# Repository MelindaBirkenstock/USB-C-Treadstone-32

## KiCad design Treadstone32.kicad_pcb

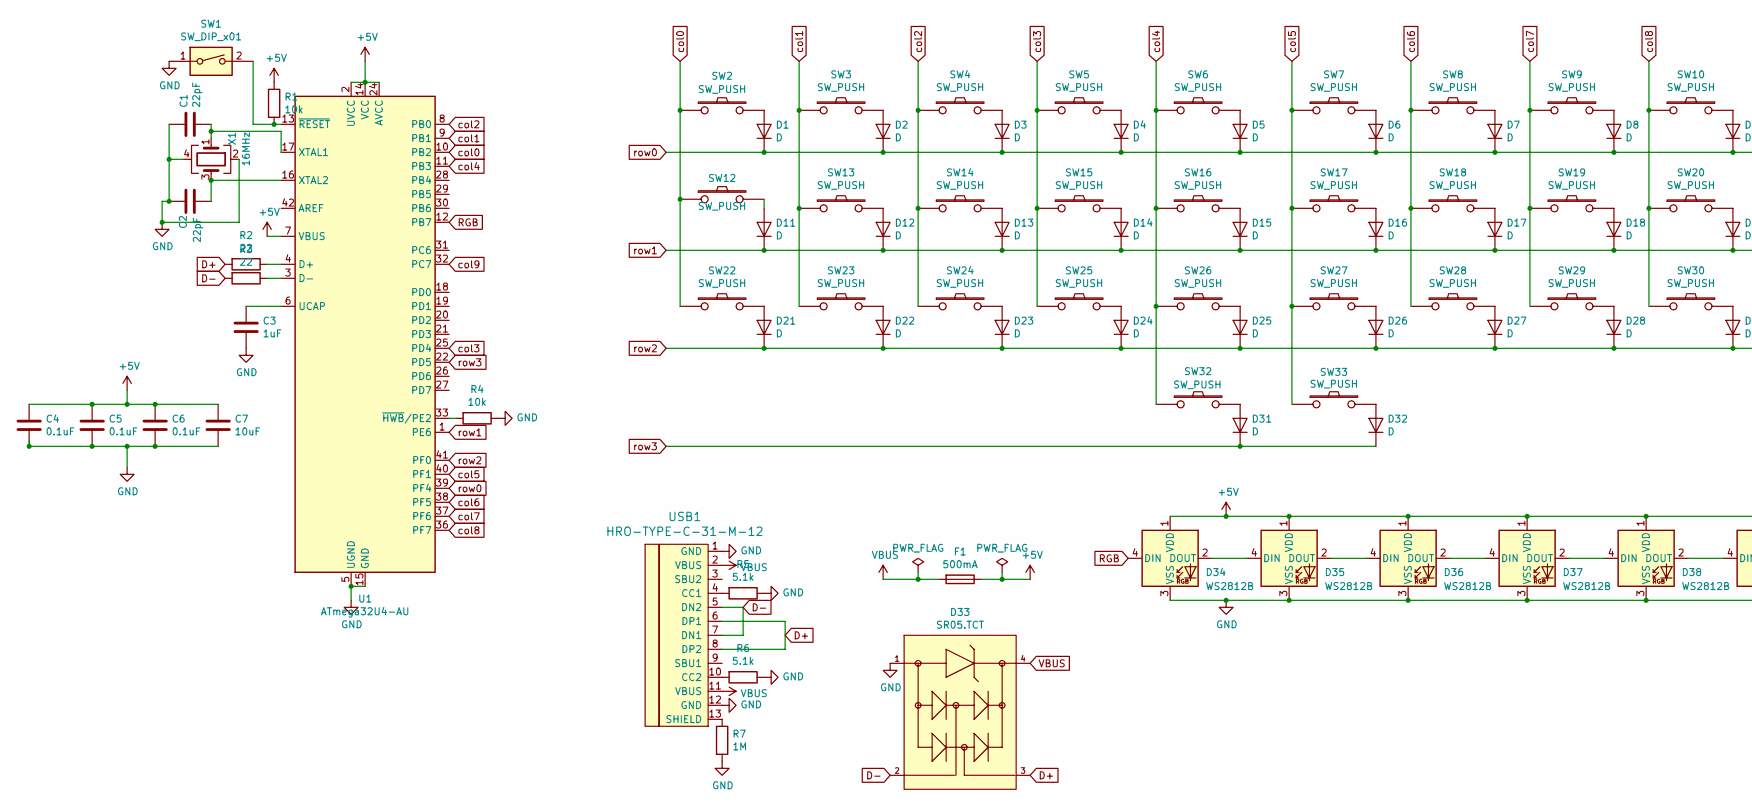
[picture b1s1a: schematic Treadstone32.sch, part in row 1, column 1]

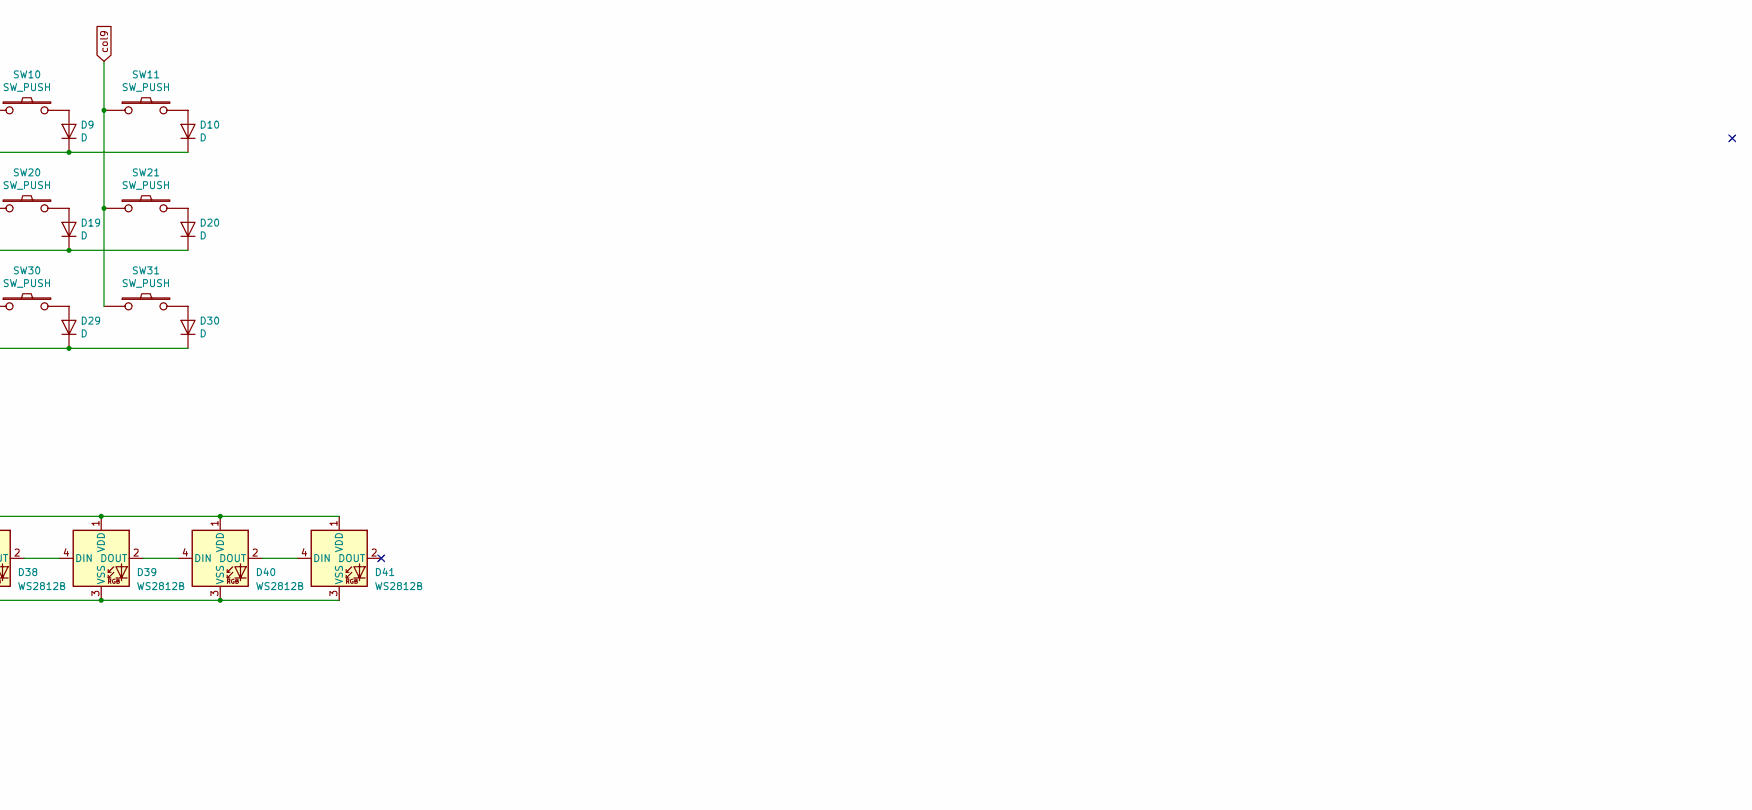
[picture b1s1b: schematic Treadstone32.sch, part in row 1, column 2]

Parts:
C1, C2: 22pF; C_0805_2012Metric
C3: 1uF; C_0805_2012Metric
C4, C5, C6: 0.1uF; C_0805_2012Metric
C7: 10uF; C_0805_2012Metric
D1, D2, D3, D4, D5, D6, D7, D8, D9, D10, D11, D12, D13, D14, D15, D16, D17, D18, D19, D20, D21, D22, D23, D24, D25, D26, D27, D28, D29, D30, D31, D32: D; D_SOD-123
D33: SR05.TCT; Semtech-SOT-143-0-0-MFG; breakdown voltage 6V; clamping voltage 20V; mouser part number 947-SR05.TCT; digikey description TVS DIODE 5V 20V SOT143-4
D34, D35, D36, D37, D38, D39, D40, D41: WS2812B; LED_WS2812B_PLCC4_5.0x5.0mm_P3.2mm
F1: 500mA; Fuse_0805_2012Metric
R1, R4: 10k; R_0805_2012Metric
R2, R3: 22; R_0805_2012Metric
R5, R6: 5.1k; R_0805_2012Metric
R7: 1M; R_0805_2012Metric
SW1: SW_DIP_x01; PinHeader_1x02_P2.00mm_Vertical
SW2, SW3, SW4, SW5, SW6, SW7, SW8, SW9, SW10, SW11, SW12, SW13, SW14, SW15, SW16, SW17, SW18, SW19, SW20, SW21, SW22, SW23, SW24, SW25, SW26, SW27, SW28, SW29, SW30, SW31, SW32, SW33: SW_PUSH; MXOnly-1U-NoLED
U1: ATmega32U4-AU; TQFP-44_10x10mm_P0.8mm
USB1: HRO-TYPE-C-31-M-12; HRO-TYPE-C-31-M-12-HandSoldering
X1: 16MHz; Crystal_SMD_3225-4Pin_3.2x2.5mm_HandSoldering

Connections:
+5V: C4.1, C5.1, C6.1, C7.1, D34.1 (VDD), D35.1 (VDD), D36.1 (VDD), D37.1 (VDD), D38.1 (VDD), D39.1 (VDD), D40.1 (VDD), D41.1 (VDD), F1.1, R1.1, U1.2 (UVCC), U1.7 (VBUS), U1.14 (VCC), U1.24 (AVCC), U1.34 (VCC), U1.44 (AVCC)
D+: D33.3 (2_I/O), R2.2, USB1.6 (DP1), USB1.8 (DP2)
D-: D33.2 (1_I/O), R3.2, USB1.5 (DN2), USB1.7 (DN1)
GND: C1.1, C2.1, C3.2, C4.2, C5.2, C6.2, C7.2, D33.1 (ANODE), D34.3 (VSS), D35.3 (VSS), D36.3 (VSS), D37.3 (VSS), D38.3 (VSS), D39.3 (VSS), D40.3 (VSS), D41.3 (VSS), R4.1, R5.1, R6.1, R7.2, SW1.1, U1.5 (UGND), U1.15 (GND), U1.23 (GND), U1.35 (GND), U1.43 (GND), USB1.1 (GND), USB1.12 (GND), X1.2, X1.4
unnamed: C1.2, U1.17 (XTAL1), X1.1
unnamed: C2.2, U1.16 (XTAL2), X1.3
unnamed: C3.1, U1.6 (UCAP)
unnamed: D1.2 (A), SW2.2
unnamed: D2.2 (A), SW3.2
unnamed: D3.2 (A), SW4.2
unnamed: D4.2 (A), SW5.2
unnamed: D5.2 (A), SW6.2
unnamed: D6.2 (A), SW7.2
unnamed: D7.2 (A), SW8.2
unnamed: D8.2 (A), SW9.2
unnamed: D9.2 (A), SW10.2
unnamed: D10.2 (A), SW11.2
unnamed: D11.2 (A), SW12.2
unnamed: D12.2 (A), SW13.2
unnamed: D13.2 (A), SW14.2
unnamed: D14.2 (A), SW15.2
unnamed: D15.2 (A), SW16.2
unnamed: D16.2 (A), SW17.2
unnamed: D17.2 (A), SW18.2
unnamed: D18.2 (A), SW19.2
unnamed: D19.2 (A), SW20.2
unnamed: D20.2 (A), SW21.2
unnamed: D21.2 (A), SW22.2
unnamed: D22.2 (A), SW23.2
unnamed: D23.2 (A), SW24.2
unnamed: D24.2 (A), SW25.2
unnamed: D25.2 (A), SW26.2
unnamed: D26.2 (A), SW27.2
unnamed: D27.2 (A), SW28.2
unnamed: D28.2 (A), SW29.2
unnamed: D29.2 (A), SW30.2
unnamed: D30.2 (A), SW31.2
unnamed: D31.2 (A), SW32.2
unnamed: D32.2 (A), SW33.2
unnamed: D34.2 (DOUT), D35.4 (DIN)
unnamed: D35.2 (DOUT), D36.4 (DIN)
unnamed: D36.2 (DOUT), D37.4 (DIN)
unnamed: D37.2 (DOUT), D38.4 (DIN)
unnamed: D38.2 (DOUT), D39.4 (DIN)
unnamed: D39.2 (DOUT), D40.4 (DIN)
unnamed: D40.2 (DOUT), D41.4 (DIN)
unnamed: R1.2, SW1.2, U1.13 (~RESET)
unnamed: R2.1, U1.4 (D+)
unnamed: R3.1, U1.3 (D-)
unnamed: R4.2, U1.33 (~HWB~/PE2)
unnamed: R5.2, USB1.4 (CC1)
unnamed: R6.2, USB1.10 (CC2)
unnamed: R7.1, USB1.13 (SHIELD)
RGB: D34.4 (DIN), U1.12 (PB7)
VBUS: D33.4 (CATHODE), F1.2, USB1.2 (VBUS), USB1.11 (VBUS)
col0: SW2.1, SW12.1, SW22.1, U1.10 (PB2)
col1: SW3.1, SW13.1, SW23.1, U1.9 (PB1)
col2: SW4.1, SW14.1, SW24.1, U1.8 (PB0)
col3: SW5.1, SW15.1, SW25.1, U1.25 (PD4)
col4: SW6.1, SW16.1, SW26.1, SW32.1, U1.11 (PB3)
col5: SW7.1, SW17.1, SW27.1, SW33.1, U1.40 (PF1)
col6: SW8.1, SW18.1, SW28.1, U1.38 (PF5)
col7: SW9.1, SW19.1, SW29.1, U1.37 (PF6)
col8: SW10.1, SW20.1, SW30.1, U1.36 (PF7)
col9: SW11.1, SW21.1, SW31.1, U1.32 (PC7)
row0: D1.1 (K), D2.1 (K), D3.1 (K), D4.1 (K), D5.1 (K), D6.1 (K), D7.1 (K), D8.1 (K), D9.1 (K), D10.1 (K), U1.39 (PF4)
row1: D11.1 (K), D12.1 (K), D13.1 (K), D14.1 (K), D15.1 (K), D16.1 (K), D17.1 (K), D18.1 (K), D19.1 (K), D20.1 (K), U1.1 (PE6)
row2: D21.1 (K), D22.1 (K), D23.1 (K), D24.1 (K), D25.1 (K), D26.1 (K), D27.1 (K), D28.1 (K), D29.1 (K), D30.1 (K), U1.41 (PF0)
row3: D31.1 (K), D32.1 (K), U1.22 (PD5)

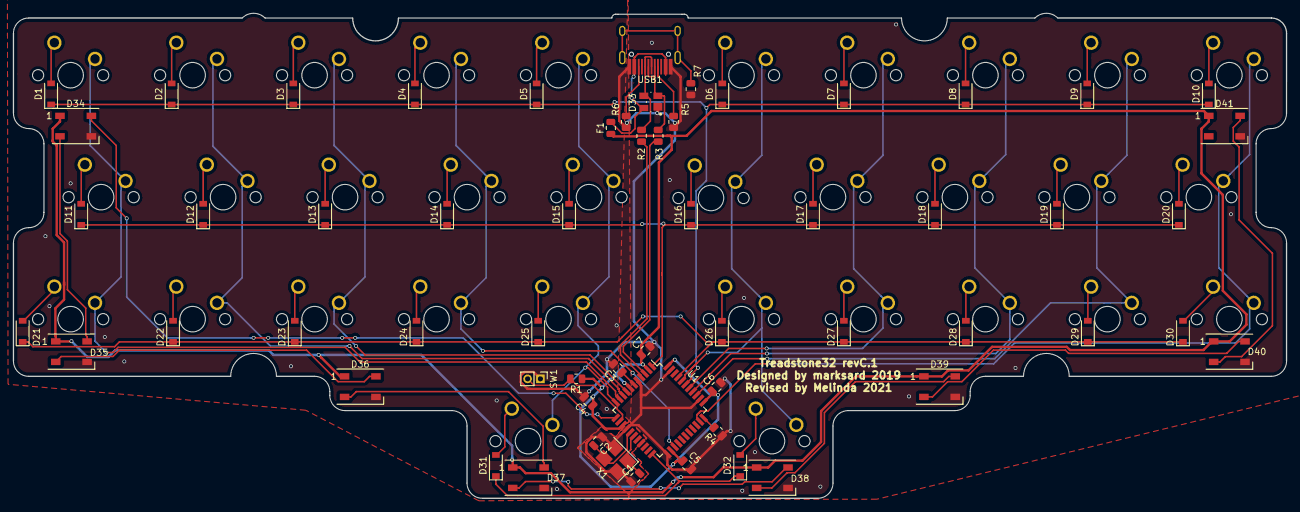
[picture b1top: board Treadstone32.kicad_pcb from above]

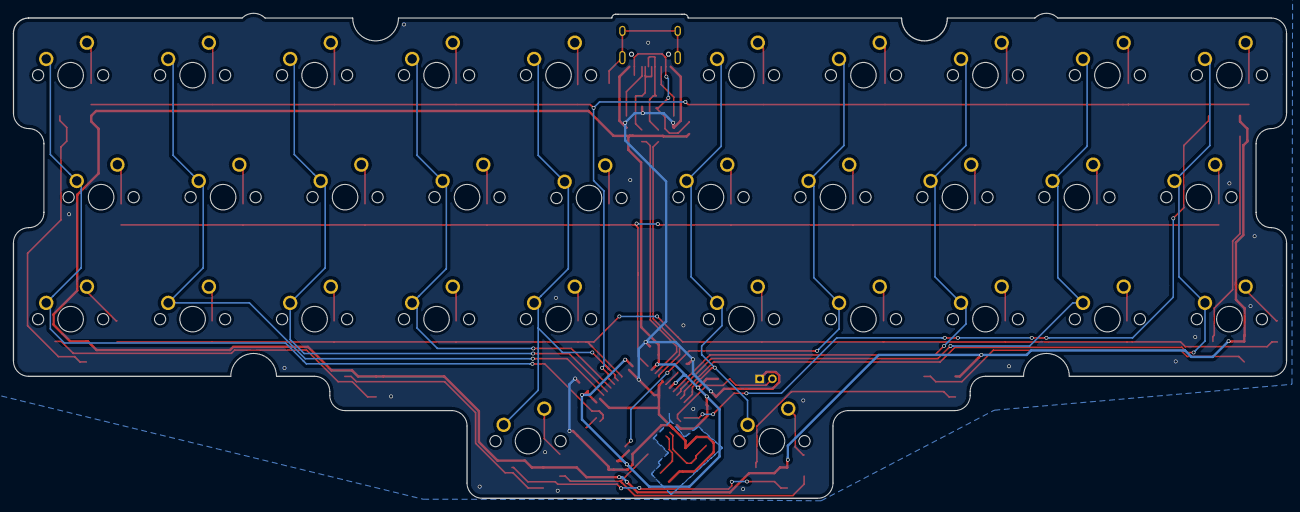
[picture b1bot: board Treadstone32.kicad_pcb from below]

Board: 2 copper layers, 198.8 x 75.7 mm, 92 parts (32 on the bottom side), 69 nets.

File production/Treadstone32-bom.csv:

"Designator","Quantity",Value,Package,LCSC Part #
"C2, C1, ","2",22pF,0805,C1804
"C3, ","1",1uF,0805,C28323
"C4, C5, C6, ","3",0.1uF,0805,C49678
"C7, ","1",10uF,0805,C15850
"D1, D2, D3, D4, D5, D11, D12, D13, D14, D15, D21, D22, D23, D24, D25, D31, D6, D7, D8, D9, D10, D16, D17, D18, D19, D20, D26, D27, D28, D29, D30, D32, ","32",D,SOD-123,C64898
"D33, ","1",SR05.TCT,SOT-143,C521962
"D34, D35, D36, D37, D38, D39, D41, D40, ","8",WS2812B,SMD 5x5,
"F1, ","1",500mA,0805,C66452
"R2, R3, ","2",22,0805,C17561
"R4, R1, ","2",10k,0805,C17414
"R5, R6, ","2",5.1k,0805,C27834
"R7, ","1",1M,0805,C17514
"U1, ","1",ATmega32U4-AU,TQFP-44 10x10mm,C44854
"USB1, ","1",HRO-TYPE-C-31-M-12,,C165948
"X1, ","1",16MHz,3225,C13738

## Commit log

2021-01-28 First push
    Initial push of my variant of the treadstone32 that has usb-c and some modifications.
2021-02-22 Pcb edits
2021-03-13 Add underglow and switch to solderable switches
2021-03-13 Cleanup refs
